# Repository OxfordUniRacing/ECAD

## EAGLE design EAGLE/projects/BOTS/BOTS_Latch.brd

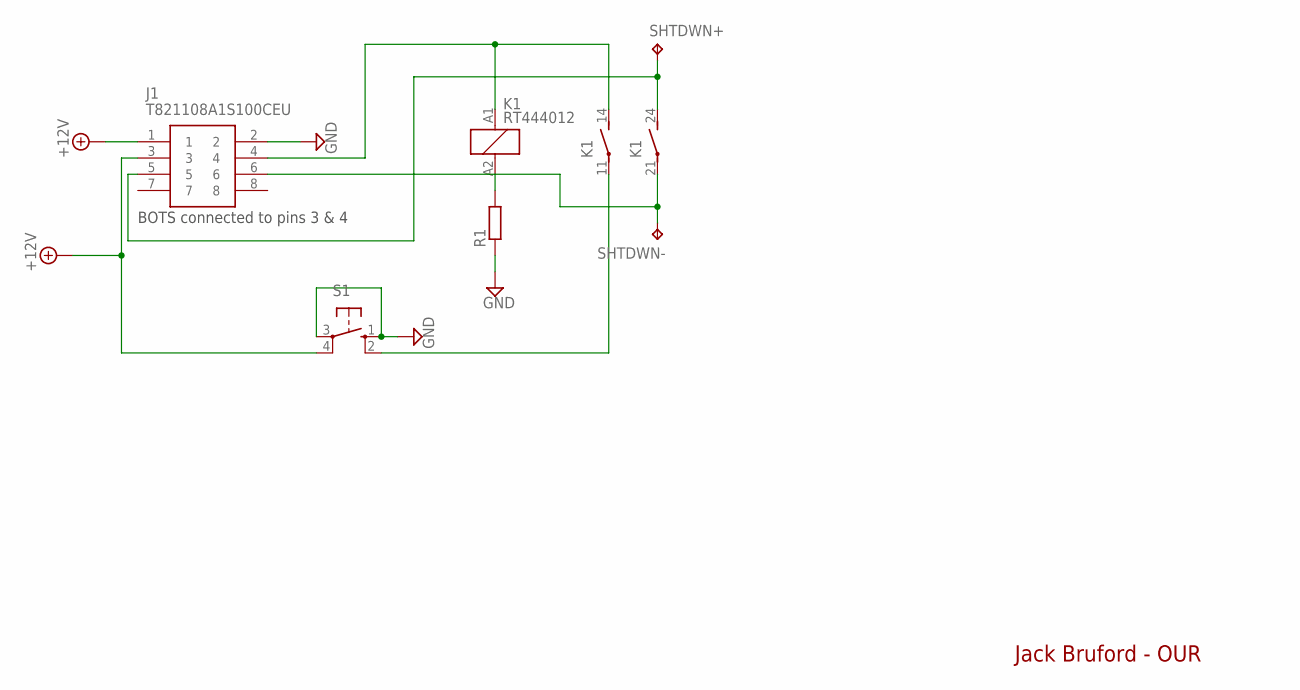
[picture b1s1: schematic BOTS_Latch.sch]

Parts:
J1: T821108A1S100CEU; HDRV8W64P254_2X4_1778X895X915P
K1: RT444012; RT2N/O
R1: R-EU_0207/15; 0207/15
S1: 10-XX; B3F-10XX
SHTDWN+: TPPAD1-13; P1-13
SHTDWN-: TPPAD1-13; P1-13

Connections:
+12V: J1.1, J1.3, S1.4 (P1)
GND: J1.2, R1.1, S1.1 (S), S1.3
unnamed: K1.11, S1.2 (S1)
unnamed: K1.A2 (2), R1.2
unnamed: J1.5, K1.24 (S), SHTDWN+.TP
unnamed: J1.6, K1.21, SHTDWN-.TP
unnamed: J1.4, K1.14 (S), K1.A1 (1)

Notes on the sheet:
BOTS connected to pins 3 & 4
Jack Bruford - OUR

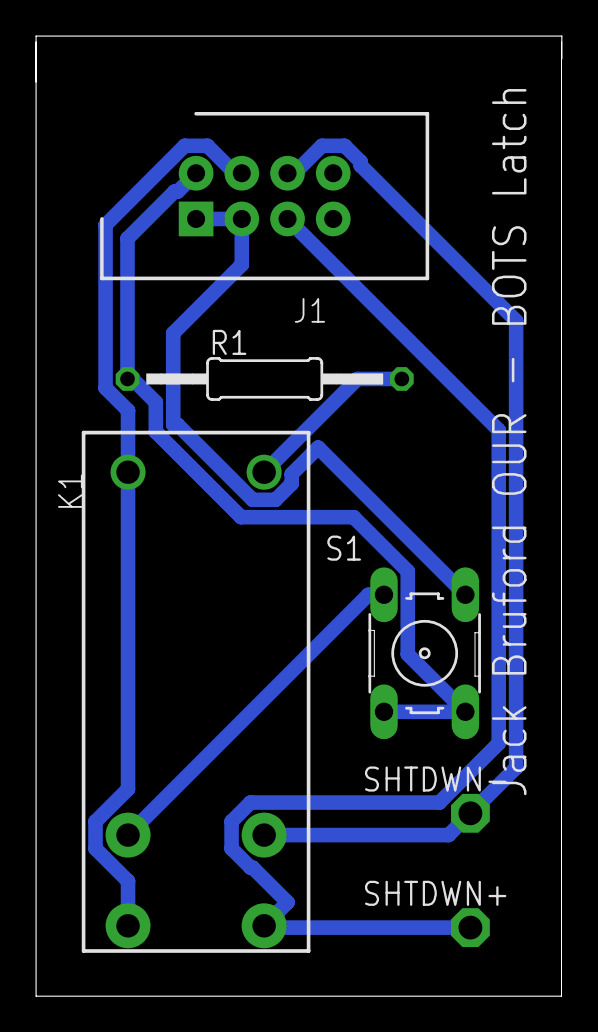
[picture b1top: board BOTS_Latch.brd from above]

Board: 2 copper layers, 29.2 x 53.3 mm, 6 parts (0 on the bottom side), 7 nets.

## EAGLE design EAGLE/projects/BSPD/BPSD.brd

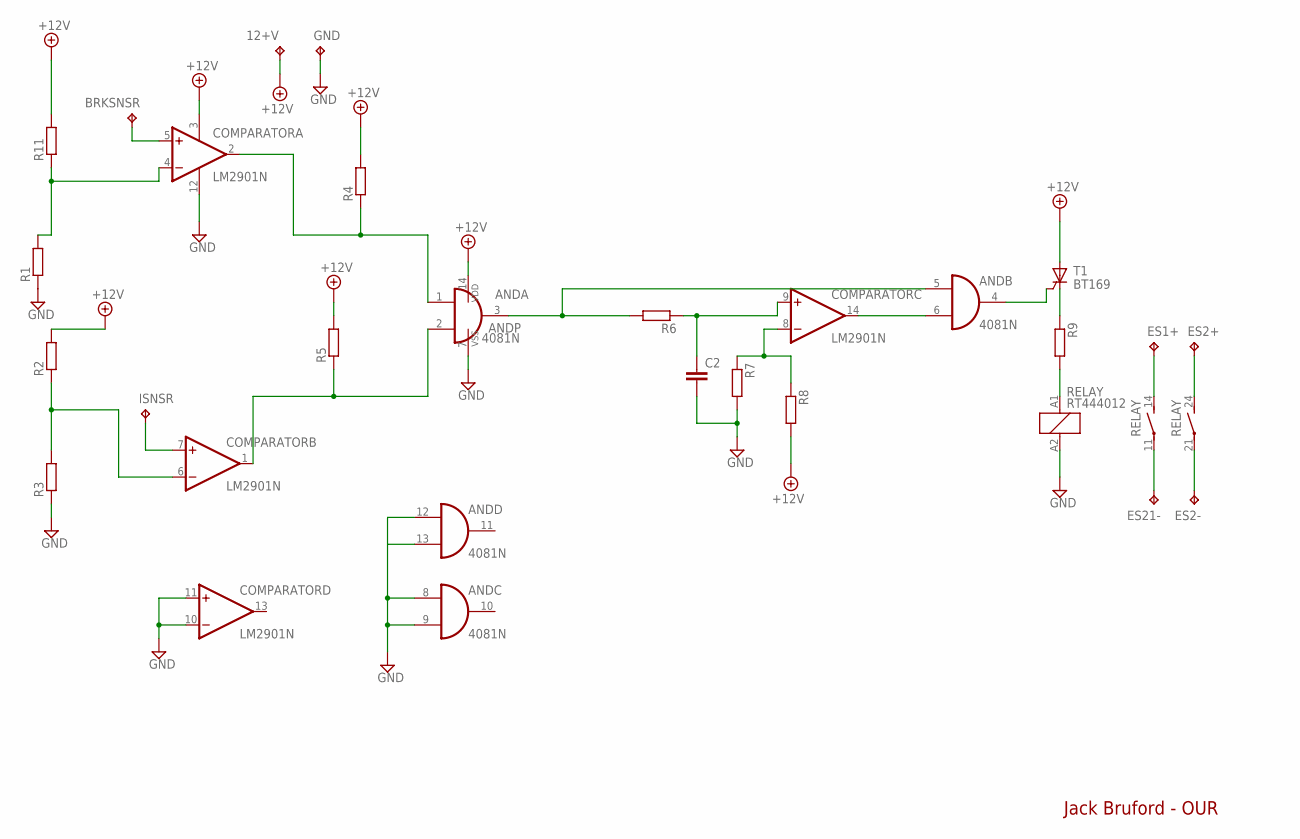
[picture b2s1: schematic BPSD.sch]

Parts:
12+V: TPPAD1-13; P1-13
AND: 4081N; DIL14
BRKSNSR: TPPAD1-13; P1-13
C2: C-EU050-024X044; C050-024X044
COMPARATOR: LM2901N; DIL14
ES1+, ES2+, ES2-, ES21-: TPPAD1-13; P1-13
GND: TPPAD1-13; P1-13
ISNSR: TPPAD1-13; P1-13
R1, R2, R3, R4, R5, R6, R7, R8, R9, R11: R-EU_0207/15; 0207/15
RELAY: RT444012; RT2N/O
T1: BT169; TO92-2

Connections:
+12V: 12+V.TP, AND.14 (VDD), COMPARATOR.3 (V+), R2.2, R4.2, R5.2, R8.2, R11.2, T1.A
GND: AND.7 (VSS), AND.8 (I0), AND.9 (I1), AND.12 (I0), AND.13 (I1), C2.2, COMPARATOR.10 (-IN), COMPARATOR.11 (+IN), COMPARATOR.12 (V-), GND.TP, R1.1, R3.1, R7.2, RELAY.A2 (2)
unnamed: COMPARATOR.4 (-IN), R1.2, R11.1
unnamed: AND.1 (I0), COMPARATOR.2 (OUT), R4.1
unnamed: COMPARATOR.6 (-IN), R2.1, R3.2
unnamed: AND.2 (I1), COMPARATOR.1 (OUT), R5.1
unnamed: COMPARATOR.8 (-IN), R7.1, R8.1
unnamed: AND.3 (O), AND.5 (I0), R6.2
unnamed: C2.1, COMPARATOR.9 (+IN), R6.1
unnamed: AND.6 (I1), COMPARATOR.14 (OUT)
unnamed: AND.4 (O), T1.G
unnamed: R9.1, T1.C
unnamed: R9.2, RELAY.A1 (1)
unnamed: BRKSNSR.TP, COMPARATOR.5 (+IN)
unnamed: COMPARATOR.7 (+IN), ISNSR.TP
unnamed: ES1+.TP, RELAY.14 (S)
unnamed: ES21-.TP, RELAY.11
unnamed: ES2+.TP, RELAY.24 (S)
unnamed: ES2-.TP, RELAY.21

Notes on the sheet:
Jack Bruford - OUR

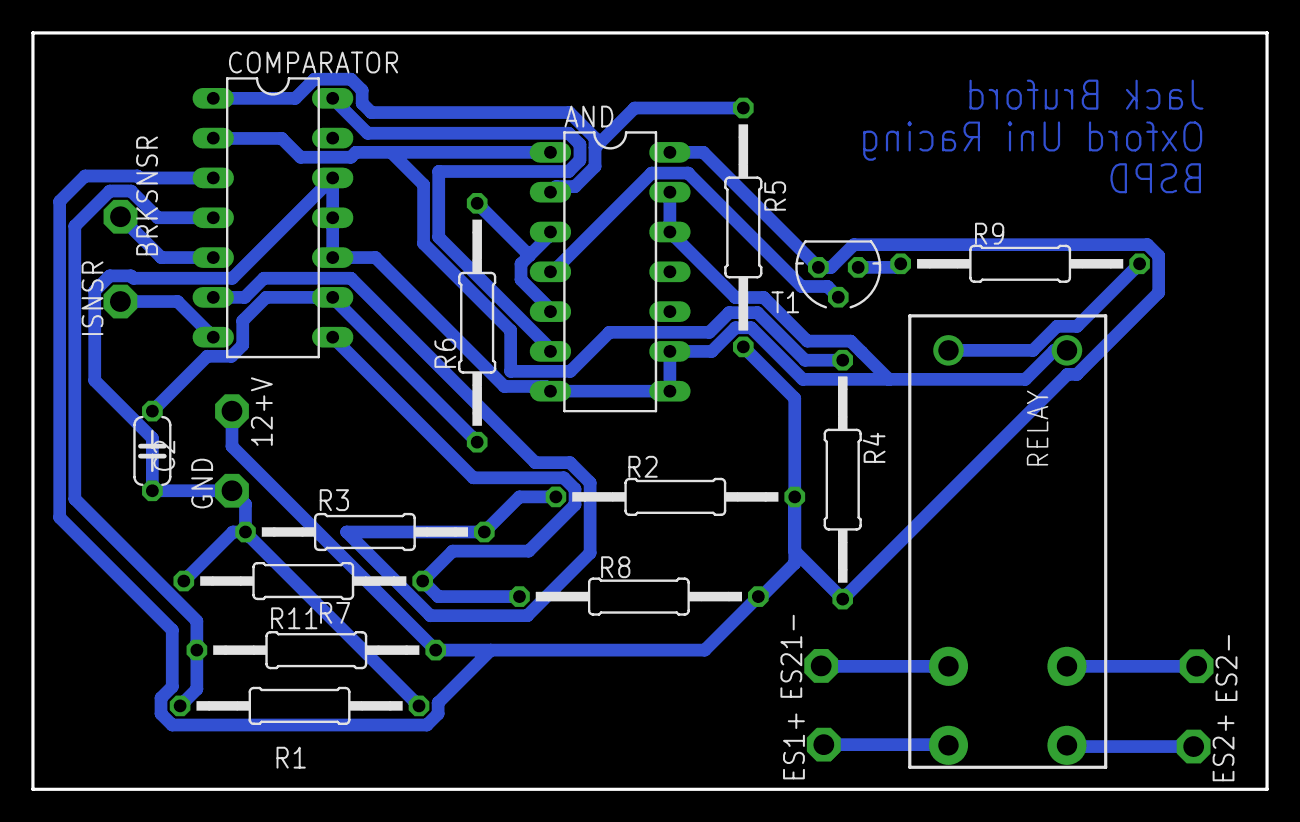
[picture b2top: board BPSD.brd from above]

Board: 2 copper layers, 78.7 x 48.3 mm, 23 parts (0 on the bottom side), 19 nets.

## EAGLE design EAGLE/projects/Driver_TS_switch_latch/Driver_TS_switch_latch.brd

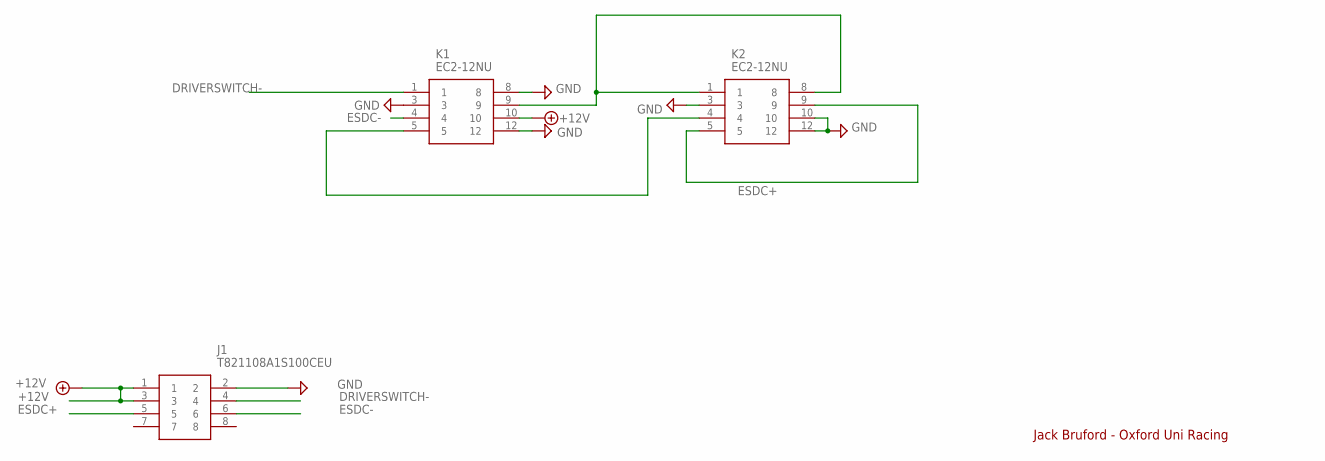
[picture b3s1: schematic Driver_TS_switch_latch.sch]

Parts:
J1: T821108A1S100CEU; HDRV8W64P254_2X4_1778X895X915P
K1, K2: EC2-12NU

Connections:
+12V: J1.1, J1.3, K1.10
DRIVERSWITCH-: J1.4, K1.1
ESDC+: J1.5, K2.5, K2.9
ESDC-: J1.6, K1.4
GND: J1.2, K1.3, K1.8, K1.12, K2.3, K2.10, K2.12
unnamed: K1.5, K2.4
unnamed: K1.9, K2.1, K2.8

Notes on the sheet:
Jack Bruford - Oxford Uni Racing

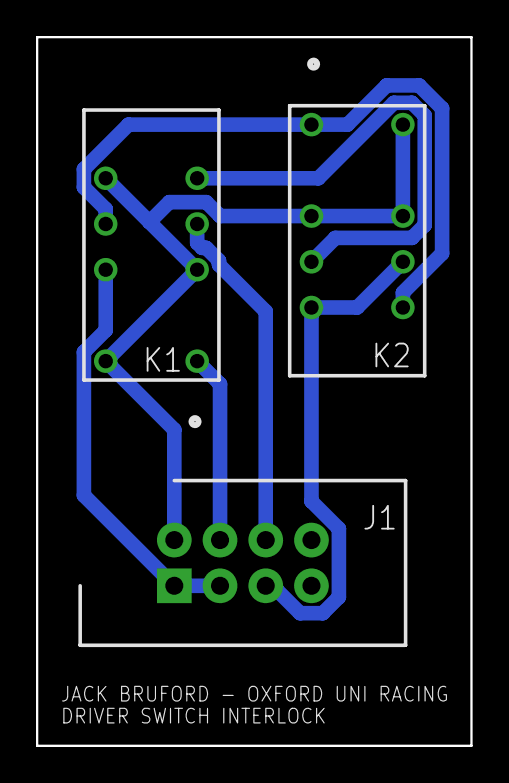
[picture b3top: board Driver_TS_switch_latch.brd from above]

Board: 2 copper layers, 24.1 x 39.4 mm, 3 parts (0 on the bottom side), 7 nets.

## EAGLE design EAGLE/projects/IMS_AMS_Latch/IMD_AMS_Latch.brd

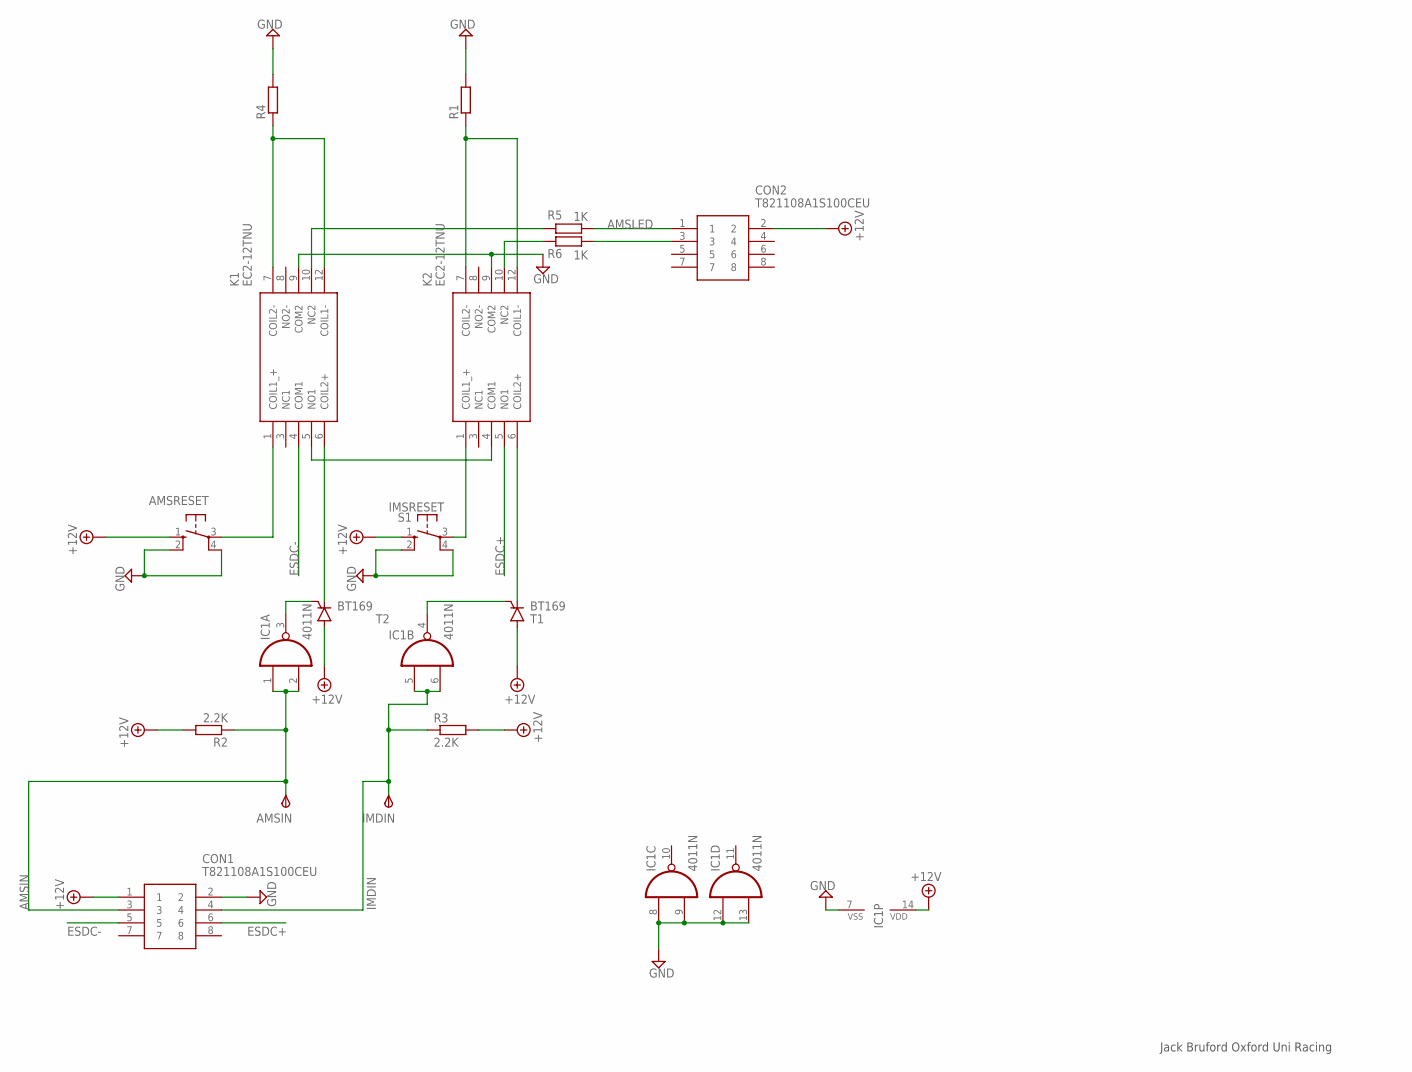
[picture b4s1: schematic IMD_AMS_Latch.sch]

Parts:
AMSIN: TPSPAD1-13; P1-13
AMSRESET: 10-XX; B3F-10XX
CON1, CON2: T821108A1S100CEU; HDRV8W64P254_2X4_1778X895X915P
IC1: 4011N; DIL14
IMDIN: TPSPAD1-13; P1-13
K1, K2: EC2-12TNU; EC212TNU
R1, R4: R-EU_0207/15; 0207/15
R2, R3: 2.2K; 0207/15
R5, R6: 1K; 0207/15
S1: 10-XX; B3F-10XX
T1, T2: BT169; TO92-2

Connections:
+12V: AMSRESET.1 (S), CON1.1, CON2.2, IC1.14 (VDD), R2.2, R3.2, S1.1 (S), T1.A, T2.A
AMSIN: AMSIN.TP, CON1.3, IC1.1 (I0), IC1.2 (I1), R2.1
AMSLED: K1.10 (NC2), R5.2
ESDC+: CON1.6, K2.5 (NO1)
ESDC-: CON1.5, K1.4 (COM1)
GND: AMSRESET.2 (S1), AMSRESET.4 (P1), CON1.2, IC1.7 (VSS), IC1.8 (I0), IC1.9 (I1), IC1.12 (I0), IC1.13 (I1), K1.9 (COM2), K2.9 (COM2), R1.2, R4.2, S1.2 (S1), S1.4 (P1)
IMDIN: CON1.4, IC1.5 (I0), IC1.6 (I1), IMDIN.TP, R3.1
IMSRESET: K1.5 (NO1), K2.4 (COM1)
unnamed: AMSRESET.3, K1.1 (COIL1_+)
unnamed: K1.6 (COIL2+), T2.C
unnamed: K2.7 (COIL2-), K2.12 (COIL1-), R1.1
unnamed: K2.6 (COIL2+), T1.C
unnamed: K2.1 (COIL1_+), S1.3
unnamed: K1.7 (COIL2-), K1.12 (COIL1-), R4.1
unnamed: K2.10 (NC2), R6.2
unnamed: CON2.1, R5.1
unnamed: CON2.3, R6.1
unnamed: IC1.3 (O), T2.G
unnamed: IC1.4 (O), T1.G

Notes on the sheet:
Jack Bruford Oxford Uni Racing

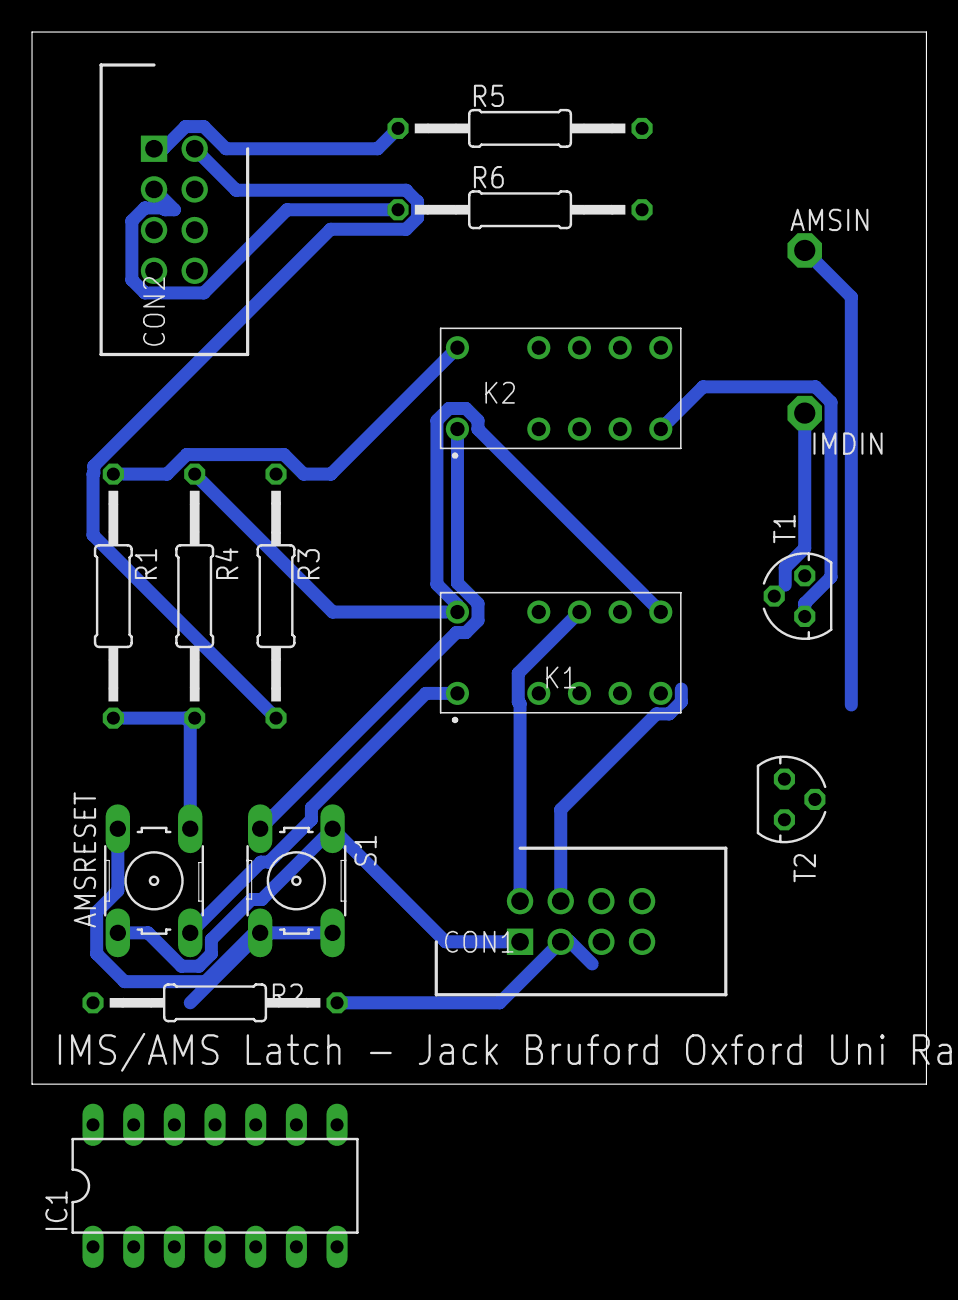
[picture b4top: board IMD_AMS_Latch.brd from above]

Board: 2 copper layers, 55.9 x 65.7 mm, 17 parts (0 on the bottom side), 19 nets.

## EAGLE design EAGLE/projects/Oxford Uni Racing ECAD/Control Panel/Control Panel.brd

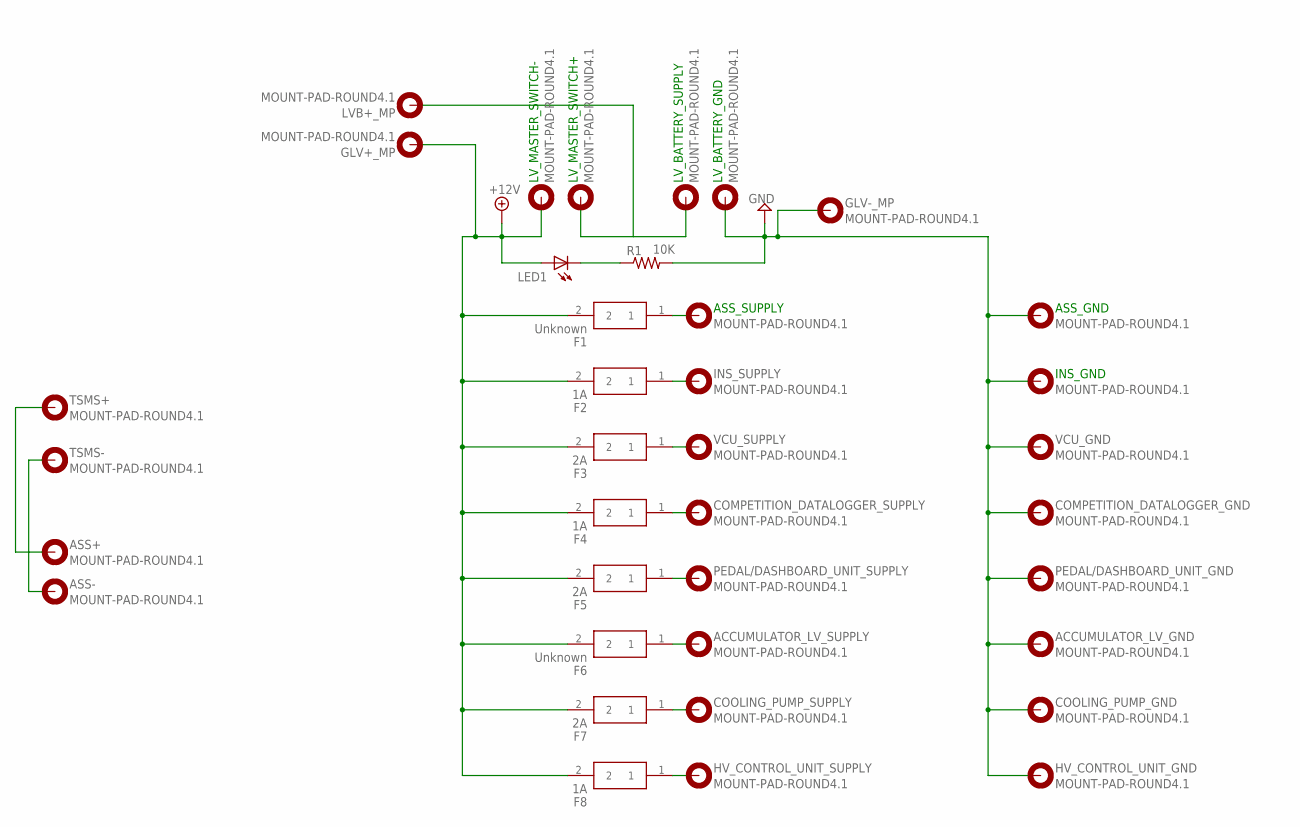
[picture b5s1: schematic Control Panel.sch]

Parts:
ACCUMULATOR_LV_GND: MOUNT-PAD-ROUND4.1; 4,1-PAD
ACCUMULATOR_LV_SUPPLY: MOUNT-PAD-ROUND4.1; 4,1-PAD
ASS+: MOUNT-PAD-ROUND4.1; 4,1-PAD
ASS-: MOUNT-PAD-ROUND4.1; 4,1-PAD
ASS_GND: MOUNT-PAD-ROUND4.1; 4,1-PAD
ASS_SUPPLY: MOUNT-PAD-ROUND4.1; 4,1-PAD
COMPETITION_DATALOGGER_GND: MOUNT-PAD-ROUND4.1; 4,1-PAD
COMPETITION_DATALOGGER_SUPPLY: MOUNT-PAD-ROUND4.1; 4,1-PAD
COOLING_PUMP_GND: MOUNT-PAD-ROUND4.1; 4,1-PAD
COOLING_PUMP_SUPPLY: MOUNT-PAD-ROUND4.1; 4,1-PAD
F1, F6: Unknown; 01530008
F2, F4, F8: 1A; 01530008
F3, F5, F7: 2A; 01530008
GLV+_MP: MOUNT-PAD-ROUND4.1; 4,1-PAD
GLV-_MP: MOUNT-PAD-ROUND4.1; 4,1-PAD
HV_CONTROL_UNIT_GND: MOUNT-PAD-ROUND4.1; 4,1-PAD
HV_CONTROL_UNIT_SUPPLY: MOUNT-PAD-ROUND4.1; 4,1-PAD
INS_GND: MOUNT-PAD-ROUND4.1; 4,1-PAD
INS_SUPPLY: MOUNT-PAD-ROUND4.1; 4,1-PAD
LED1: LED3MM
LVB+_MP: MOUNT-PAD-ROUND4.1; 4,1-PAD
LV_BATTERY_GND: MOUNT-PAD-ROUND4.1; 4,1-PAD
LV_BATTERY_SUPPLY: MOUNT-PAD-ROUND4.1; 4,1-PAD
LV_MASTER_SWITCH+: MOUNT-PAD-ROUND4.1; 4,1-PAD
LV_MASTER_SWITCH-: MOUNT-PAD-ROUND4.1; 4,1-PAD
PEDAL/DASHBOARD_UNIT_GND: MOUNT-PAD-ROUND4.1; 4,1-PAD
PEDAL/DASHBOARD_UNIT_SUPPLY: MOUNT-PAD-ROUND4.1; 4,1-PAD
R1: 10K; 0207/12
TSMS+: MOUNT-PAD-ROUND4.1; 4,1-PAD
TSMS-: MOUNT-PAD-ROUND4.1; 4,1-PAD
VCU_GND: MOUNT-PAD-ROUND4.1; 4,1-PAD
VCU_SUPPLY: MOUNT-PAD-ROUND4.1; 4,1-PAD

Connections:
+12V: F1.2, F2.2, F3.2, F4.2, F5.2, F6.2, F7.2, F8.2, GLV+_MP.B4,1, LED1.A, LV_MASTER_SWITCH-.B4,1
GND1: ACCUMULATOR_LV_GND.B4,1, ASS_GND.B4,1, COMPETITION_DATALOGGER_GND.B4,1, COOLING_PUMP_GND.B4,1, GLV-_MP.B4,1, HV_CONTROL_UNIT_GND.B4,1, INS_GND.B4,1, LV_BATTERY_GND.B4,1, PEDAL/DASHBOARD_UNIT_GND.B4,1, R1.2, VCU_GND.B4,1
unnamed: F2.1, INS_SUPPLY.B4,1
unnamed: ASS_SUPPLY.B4,1, F1.1
unnamed: F3.1, VCU_SUPPLY.B4,1
unnamed: COMPETITION_DATALOGGER_SUPPLY.B4,1, F4.1
unnamed: LVB+_MP.B4,1, LV_BATTERY_SUPPLY.B4,1, LV_MASTER_SWITCH+.B4,1
unnamed: F5.1, PEDAL/DASHBOARD_UNIT_SUPPLY.B4,1
unnamed: ACCUMULATOR_LV_SUPPLY.B4,1, F6.1
unnamed: COOLING_PUMP_SUPPLY.B4,1, F7.1
unnamed: LED1.K (C), R1.1
unnamed: ASS+.B4,1, TSMS+.B4,1
unnamed: ASS-.B4,1, TSMS-.B4,1
unnamed: F8.1, HV_CONTROL_UNIT_SUPPLY.B4,1

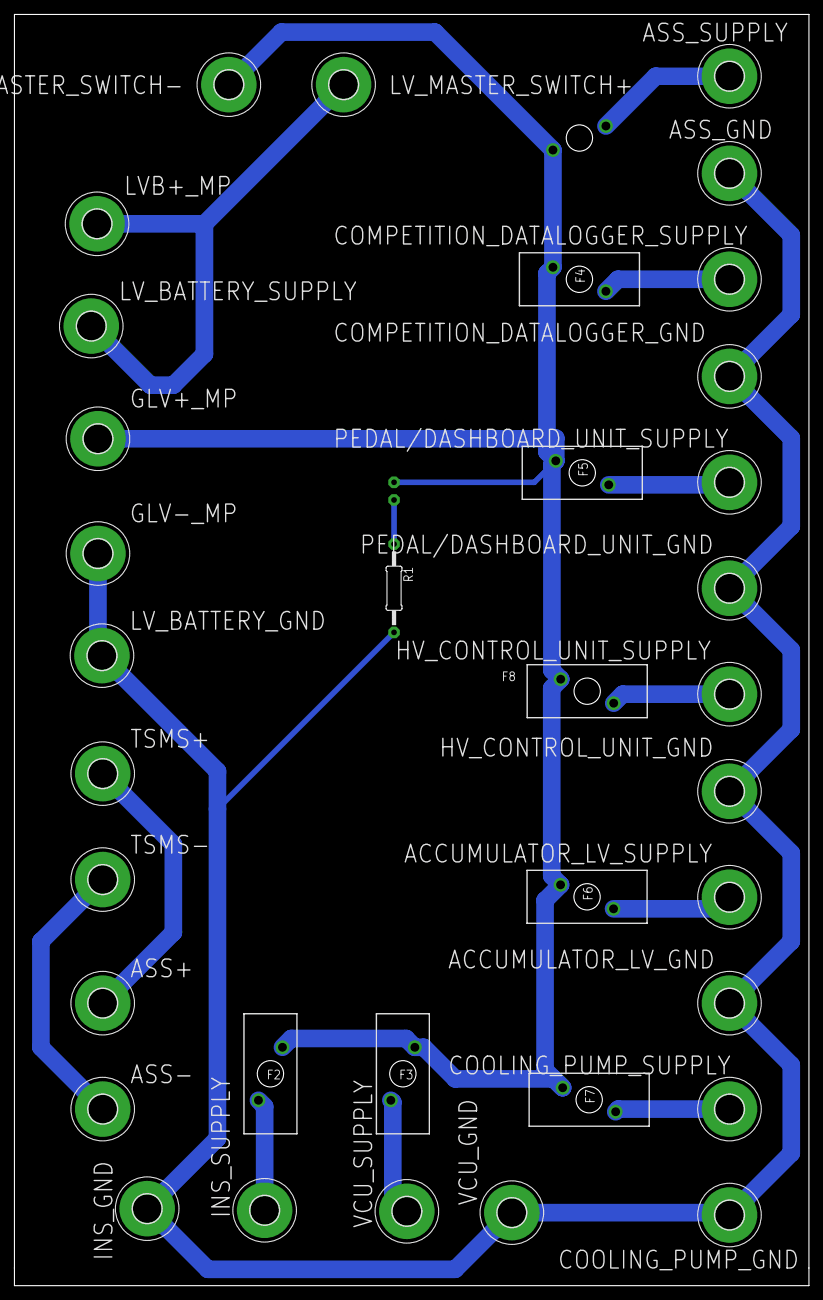
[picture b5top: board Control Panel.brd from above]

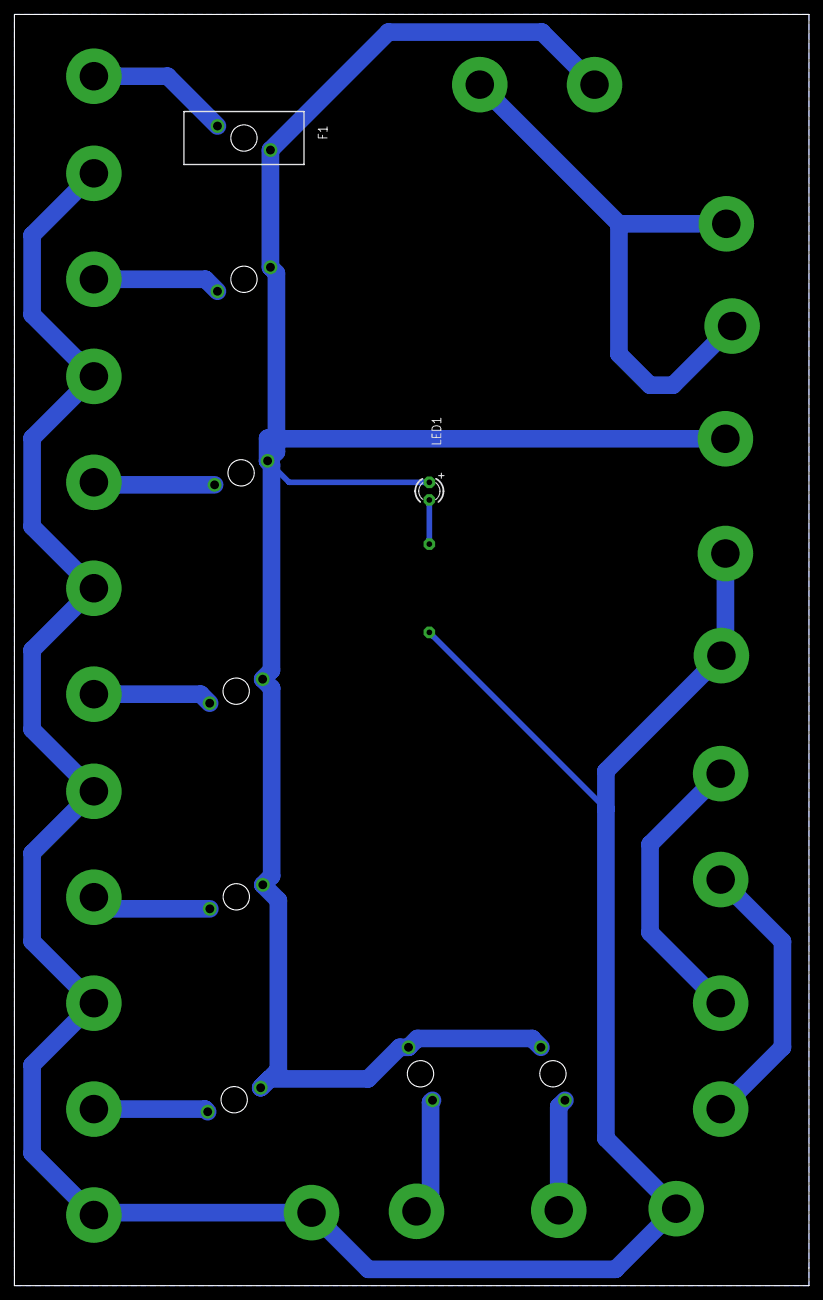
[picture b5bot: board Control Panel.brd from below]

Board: 2 copper layers, 114.3 x 182.9 mm, 37 parts (2 on the bottom side), 14 nets.

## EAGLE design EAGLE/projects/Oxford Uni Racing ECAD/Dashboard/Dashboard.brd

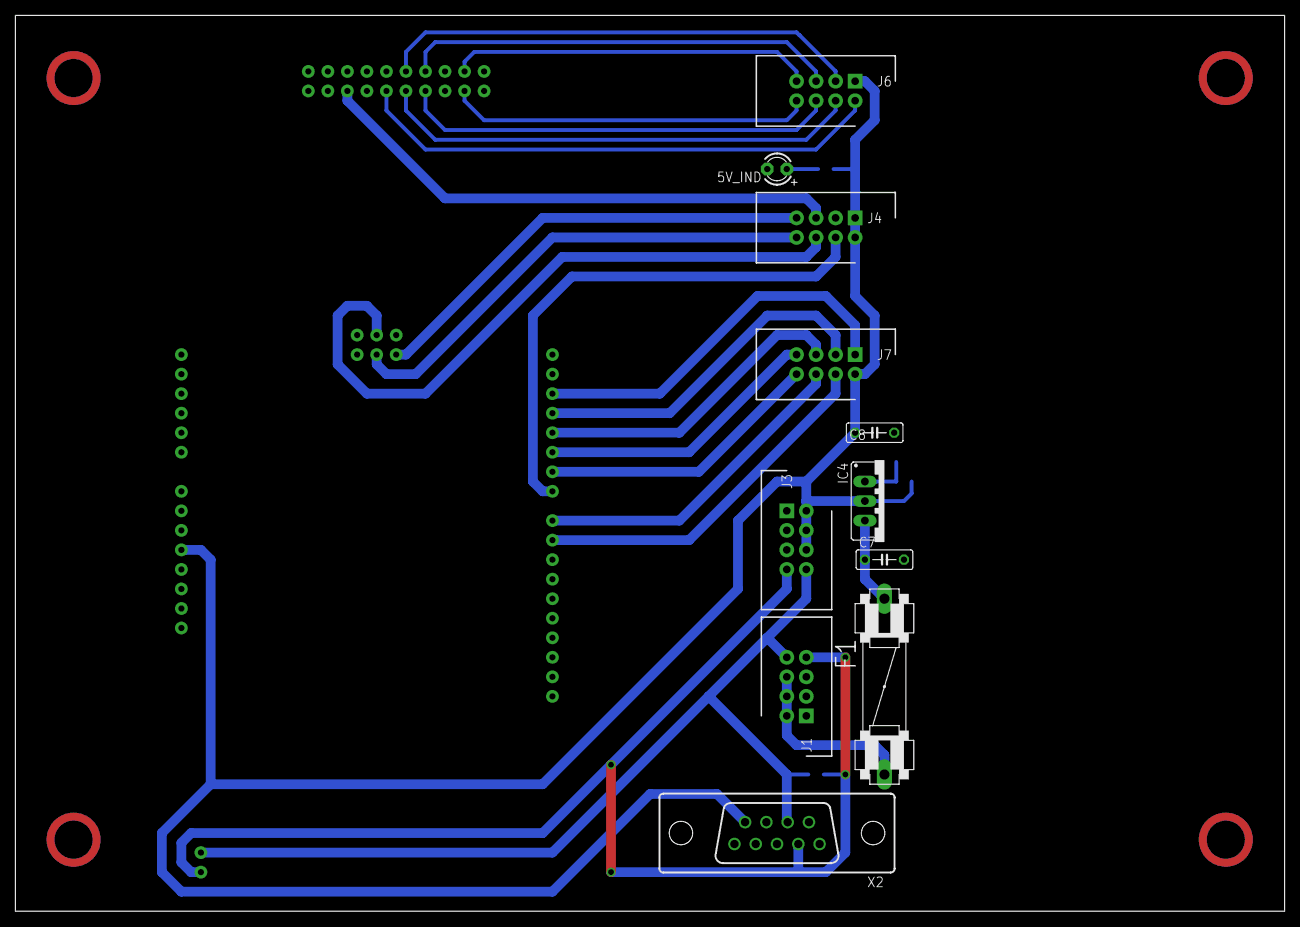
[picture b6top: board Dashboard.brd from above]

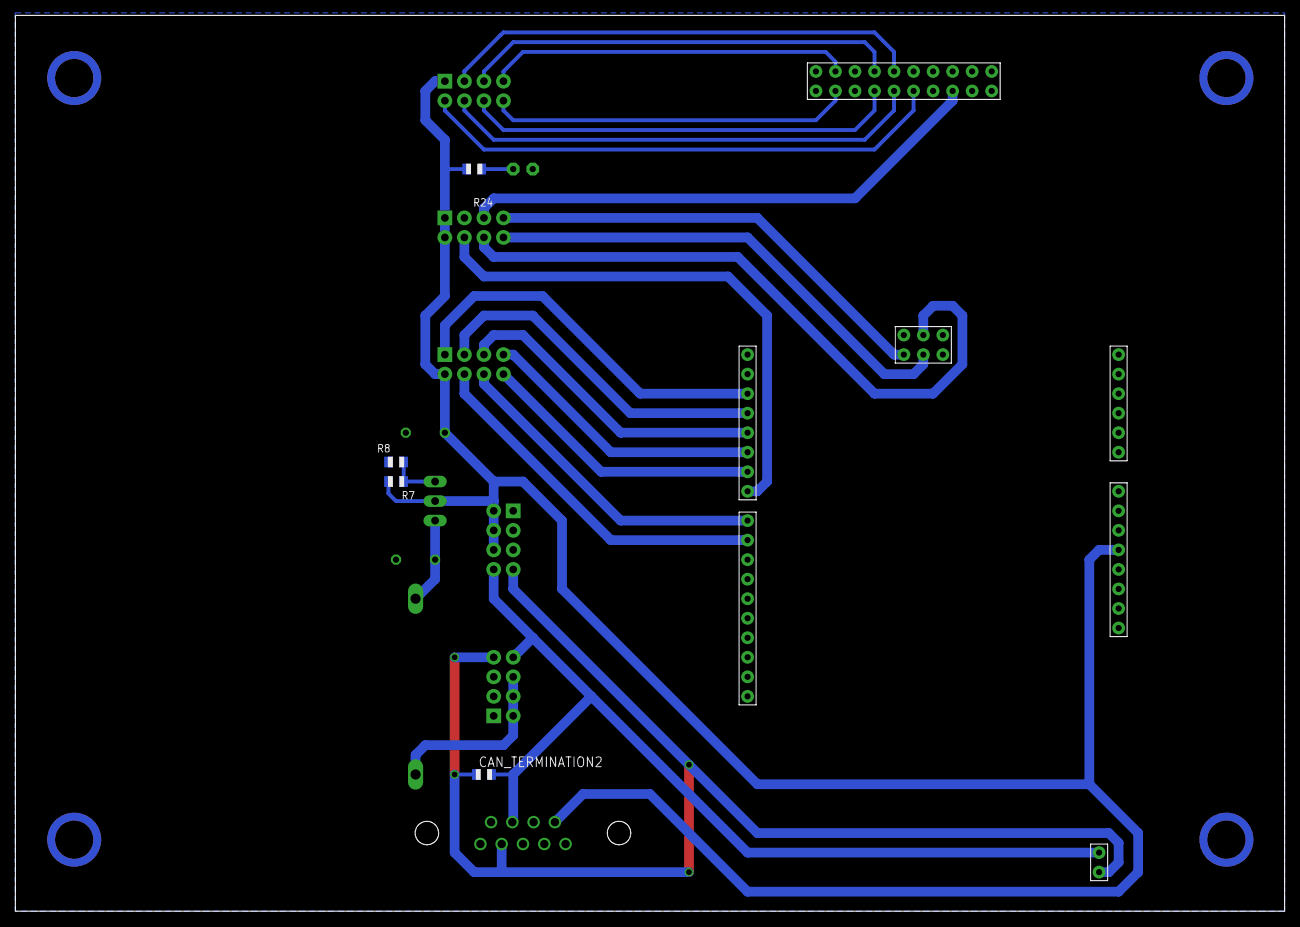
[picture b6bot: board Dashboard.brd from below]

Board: 2 copper layers, 165.1 x 116.5 mm, 16 parts (5 on the bottom side), 27 nets.

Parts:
5V_IND: LED3MM
C7: 0.1uF; C050-025X075
C8: 1uF; C050-025X075
CAN_TERMINATION2: 120; R0805
F1: 1A; FUSE
IC4: 317TS
J1: PWR_CAN; HDRV8W64P254_2X4_1778X895X915P
J3: CAN_OUT; HDRV8W64P254_2X4_1778X895X915P
J4: DISPL; HDRV8W64P254_2X4_1778X895X915P
J6, J7: BUTTONS; HDRV8W64P254_2X4_1778X895X915P
R7: 240; R0805
R8: 723; R0805
R24: 1.8K; R0805
U$1: SAMC21-XPLAINED-PRO_NO_EXT1&2
X2: D-SUB9-H2M09ST; H2M09ST

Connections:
5V: C8.1, IC4.2, J3.2, J3.4, J3.6, J4.1, J4.2, J6.1, J7.2, R7.2, R24.2, U$1.J802-4, X2.9
12V: C7.1, F1.2, IC4.3
12V_BATTERY1: F1.1, J1.2, J1.4, J1.6
CANH: CAN_TERMINATION2.2, J1.8, J3.8, U$1.CAN-0, X2.7
CANL: CAN_TERMINATION2.1, J1.7, J3.7, U$1.CAN-1, X2.2
DISPL_CS: J4.4, U$1.J804-7
DRIVER_SELECT_1: J7.8, U$1.J804-6
DRIVER_SELECT_2: J7.7, U$1.J804-5
DRIVER_SELECT_3: J7.5, U$1.J804-4
DRIVER_SELECT_4: J7.3, U$1.J804-3
DRIVER_SELECT_5: J7.1, U$1.J804-2
EVENT_SELECT_1: J6.5, U$1.EXT3-7
EVENT_SELECT_2: J6.6, U$1.EXT3-6
EVENT_SELECT_3: J6.7, U$1.EXT3-3
EVENT_SELECT_4: J6.8, U$1.EXT3-2
GND: 5V_IND.K, C7.2, C8.2, J1.1, J1.3, J1.5, J3.1, J3.3, J3.5, J4.3, R8.1, U$1.EXT3-12, U$1.EXT3-13, U$1.J802-5, U$1.J802-6, X2.3, X2.6
IGNITION_SWITCH: J6.2, U$1.EXT3-10
MISO: J4.7, U$1.J800-0
MOSI: J4.6, U$1.J800-3
unnamed: 5V_IND.A, R24.1
unnamed: IC4.1, R7.1, R8.2
PEDAL_MAPPING_1: J7.4, U$1.J801-1
PEDAL_MAPPING_2: J7.6, U$1.J801-0
PWR_REDUCTION: J6.3, U$1.EXT3-9
SCK: J4.8, U$1.J800-2
TCS_ON/OFF: J6.4, U$1.EXT3-8
TRACTIVE_SYSTEM: J4.5, U$1.EXT3-14
